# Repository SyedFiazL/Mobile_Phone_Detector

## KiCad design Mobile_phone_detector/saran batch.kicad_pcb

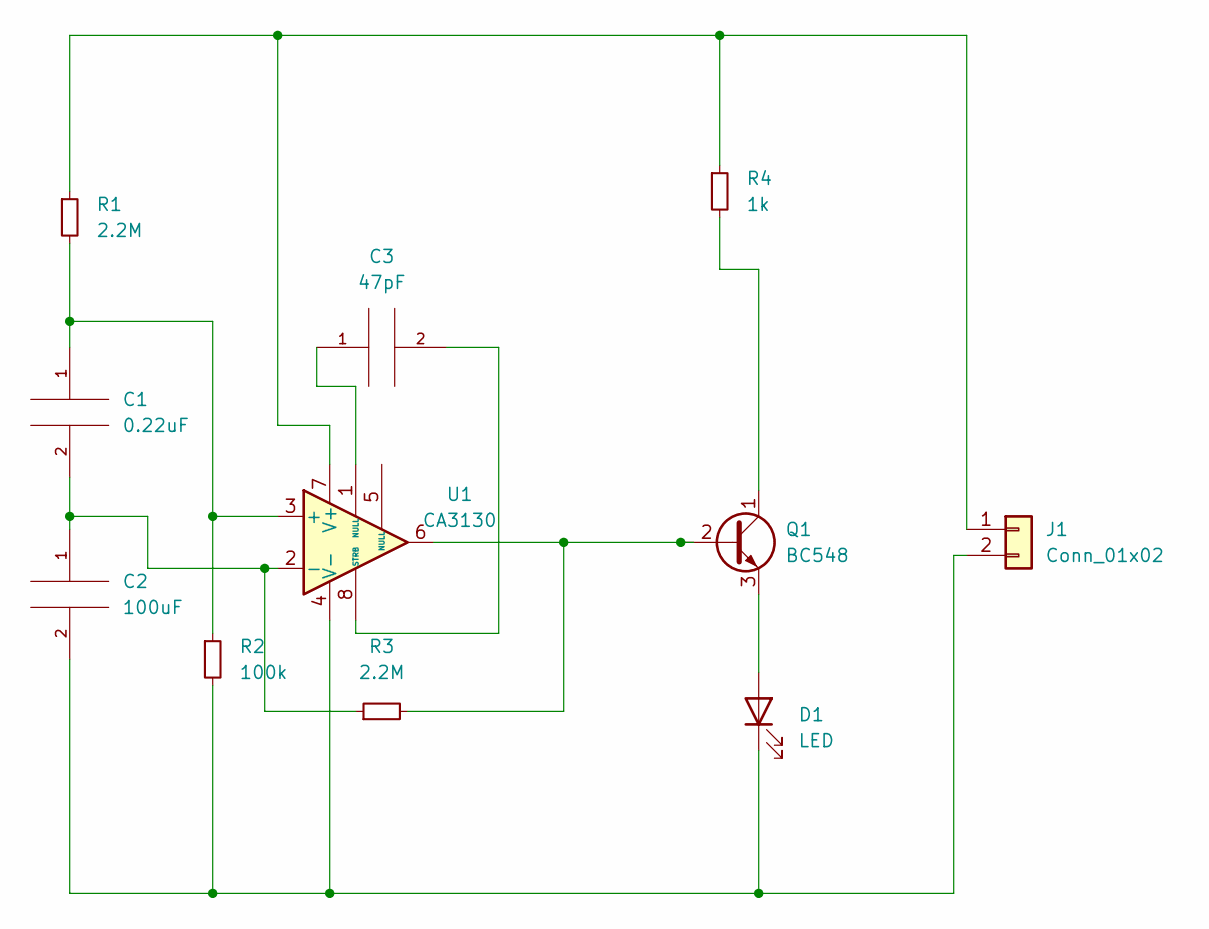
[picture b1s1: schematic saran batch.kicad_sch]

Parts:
C1: 0.22uF
C2: 100uF; CP_Axial_L10.0mm_D4.5mm_P15.00mm_Horizontal
C3: 47pF; CP_Axial_L10.0mm_D4.5mm_P15.00mm_Horizontal
D1: LED; LED_D3.0mm
J1: Conn_01x02; JWT_A3963_1x02_P3.96mm_Vertical
Q1: BC548; TO-92_Inline
R1, R3: 2.2M; R_Axial_DIN0204_L3.6mm_D1.6mm_P7.62mm_Horizontal
R2: 100k; R_Axial_DIN0204_L3.6mm_D1.6mm_P7.62mm_Horizontal
R4: 1k; R_Axial_DIN0204_L3.6mm_D1.6mm_P7.62mm_Horizontal
U1: CA3130; SOIC-8_3.9x4.9mm_P1.27mm

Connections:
unnamed: C1.1, R1.2, R2.1, U1.3 (+)
unnamed: C1.2, C2.1, R3.1, U1.2 (-)
unnamed: C2.2, D1.1 (K), J1.2, R2.2, U1.4 (V-)
unnamed: C3.1, U1.1 (NULL)
unnamed: C3.2, U1.8 (STRB)
unnamed: D1.2 (A), Q1.3 (E)
unnamed: J1.1, R1.1, R4.1, U1.7 (V+)
unnamed: Q1.1 (C), R4.2
unnamed: Q1.2 (B), R3.2, U1.6

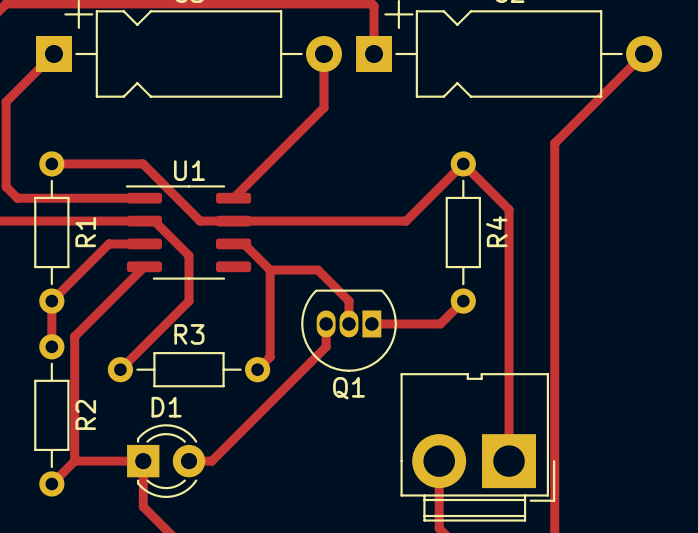
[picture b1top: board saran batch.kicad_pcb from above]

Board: 2 copper layers, 10 parts (0 on the bottom side), 9 nets.
